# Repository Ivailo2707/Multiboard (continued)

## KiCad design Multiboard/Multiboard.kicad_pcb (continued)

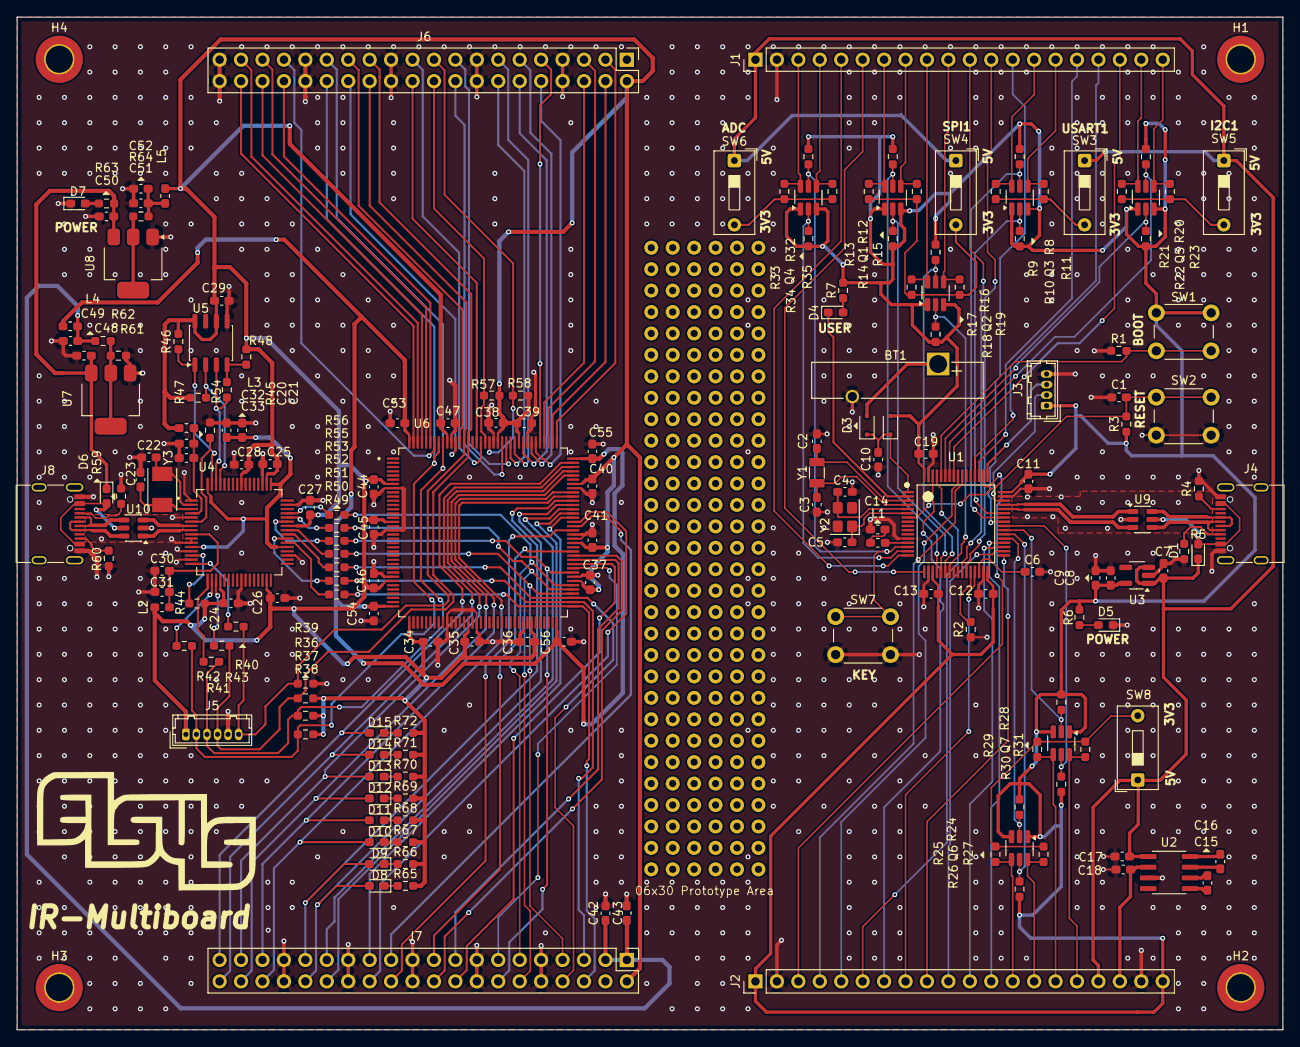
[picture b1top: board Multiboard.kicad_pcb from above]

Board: 2 copper layers, 150.0 x 120.0 mm, 190 parts (0 on the bottom side), 178 nets.

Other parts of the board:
06x30 Prototype Area: 6x30

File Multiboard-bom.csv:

"Reference","Qty","Value","DNP","Exclude from BOM","Exclude from Board","Footprint","LCSC Part Number"
"C1,C11,C12,C13,C14,C19","6","0.1u","","","","Capacitor_SMD:C_0603_1608Metric_Pad1.08x0.95mm_HandSolder","C14663"
"C2,C3","2","4.3pF","","","","Capacitor_SMD:C_0603_1608Metric_Pad1.08x0.95mm_HandSolder","C519375"
"C4,C5","2","12pF","","","","Capacitor_SMD:C_0603_1608Metric_Pad1.08x0.95mm_HandSolder","C38523"
"C6","1","2.2uF","","","","Capacitor_SMD:C_0603_1608Metric_Pad1.08x0.95mm_HandSolder","C913904"
"C7,C8,C17,C31,C33","5","4.7uF","","","","Capacitor_SMD:C_0603_1608Metric_Pad1.08x0.95mm_HandSolder","C19666"
"C9,C56","2","0.01uF","","","","Capacitor_SMD:C_0603_1608Metric_Pad1.08x0.95mm_HandSolder","C100042"
"C10,C20,C24,C25,C26,C27,C28,C29,C30,C32,C34,C35,C36,C37,C38,C39,C40,C41,C42,C43,C44,C45,C46,C47,C52,C53","26","0.1uF","","","","Capacitor_SMD:C_0603_1608Metric_Pad1.08x0.95mm_HandSolder","C14663"
"C15,C16","2","0.22uF","","","","Capacitor_SMD:C_0603_1608Metric_Pad1.08x0.95mm_HandSolder","C64705"
"C18","1","4.7uF","","","","Capacitor_SMD:C_0603_1608Metric_Pad1.08x0.95mm_HandSolder","C161217"
"C21,C48,C50,C55","4","10uF","","","","Capacitor_SMD:C_0603_1608Metric_Pad1.08x0.95mm_HandSolder","C19702"
"C22,C23","2","18pF","","","","Capacitor_SMD:C_0603_1608Metric_Pad1.08x0.95mm_HandSolder","C49326300"
"C49,C51","2","22uF","","","","Capacitor_SMD:C_0603_1608Metric_Pad1.08x0.95mm_HandSolder","C86295"
"C54","1","1uF","","","","Capacitor_SMD:C_0603_1608Metric_Pad1.08x0.95mm_HandSolder","C95843"
"D2,D3","2","D_Schottky","","","","Diode_SMD:D_SOD-323F","C2903903"
"D4,D7,D8,D9,D10,D11,D12,D13,D14,D15","10","GREEN","","","","LED_SMD:LED_0603_1608Metric_Pad1.05x0.95mm_HandSolder","C2994781"
"D5","1","RED","","","","LED_SMD:LED_0603_1608Metric_Pad1.05x0.95mm_HandSolder","C2846640"
"J4,J8","2","USB_C_Receptacle_USB2.0_16P","","","","Connector_USB:USB_C_Receptacle_G-Switch_GT-USB-7010ASV","C2988369"
"L1","1","10uH ±10%","","","","Inductor_SMD:L_0603_1608Metric_Pad1.05x0.95mm_HandSolder","C6808014"
"L2,L3,L4,L5","4","600ohm 500mA","","","","Inductor_SMD:L_0603_1608Metric_Pad1.05x0.95mm_HandSolder","C20345"
"Q1,Q2,Q3,Q4,Q5,Q6,Q7","7","Q_Dual_NMOS_G1S2G2D2S1D1","","","","Package_TO_SOT_SMD:SOT-23-6_Handsoldering","C404322"
"R1,R8,R9,R10,R11,R12,R13,R14,R15,R16,R17,R18,R19,R20,R21,R22,R23,R24,R25,R26,R27,R28,R29,R30,R31,R32,R33,R34,R35","29","10k","","","","Resistor_SMD:R_0603_1608Metric_Pad0.98x0.95mm_HandSolder","C98220"
"R2,R3,R46,R47,R48","5","10K","","","","Resistor_SMD:R_0603_1608Metric_Pad0.98x0.95mm_HandSolder","C98220"
"R4,R5,R6,R36,R37,R38,R59,R60","8","5.1K","","","","Resistor_SMD:R_0603_1608Metric_Pad0.98x0.95mm_HandSolder","C2907044"
"R7,R63,R65,R66,R67,R68,R69,R70,R71,R72","10","1K","","","","Resistor_SMD:R_0603_1608Metric_Pad0.98x0.95mm_HandSolder","C22548"
"R39,R44,R54,R57,R58","5","2.2K","","","","Resistor_SMD:R_0603_1608Metric_Pad0.98x0.95mm_HandSolder","C114662"
"R40,R41,R42,R43,R49,R50,R51,R52,R53,R55,R56,R62,R64","13","0","","","","Resistor_SMD:R_0603_1608Metric_Pad0.98x0.95mm_HandSolder","C95177"
"R45","1","12K 1%","","","","Resistor_SMD:R_0603_1608Metric_Pad0.98x0.95mm_HandSolder","C431727"
"R61","1","100","","","","Resistor_SMD:R_0603_1608Metric_Pad0.98x0.95mm_HandSolder","C105588"
"SW1","1","BOOT0","","","","Button_Switch_THT:SW_PUSH_6mm","C7528752"
"SW2","1","NRST","","","","Button_Switch_THT:SW_PUSH_6mm","C7528752"
"SW3,SW4,SW5,SW6,SW8","5","SW_SPST","","","","Button_Switch_THT:SW_DIP_SPSTx01_Slide_9.78x4.72mm_W7.62mm_P2.54mm","C41381904"
"SW7","1","KEY","","","","Button_Switch_THT:SW_PUSH_6mm","C7528752"
"U1","1","STM32F411RET6","","","","STM32F411RET6:QFP50P1200X1200X160-64N","C94355"
"U2","1","MAX662AESA_T","","","","MAX662AESA+T:SOIC127P600X175-8N","C2976348"
"U3","1","ME6211C33M5","","","","Package_TO_SOT_SMD:SOT-23-5_HandSoldering","C2984946"
"U4","1","FT2232HL-REEL","","","","FT2232HL:QFP50P1200X1200X160-64N","C27882"
"U5","1","93LCxxC","","","","Package_SO:SO-8_3.9x4.9mm_P1.27mm","C1350395"
"U7","1","AMS1117-1.2","","","","Package_TO_SOT_SMD:SOT-223","C14529"
"U8","1","NCP1117","","","","Package_TO_SOT_SMD:SOT-223","C20546"
"U9,U10","2","USBLC6-2SC6","","","","Package_TO_SOT_SMD:SOT-23-6","C7519"
"Y1","1","32.768KHz","","","","Crystal:Crystal_SMD_3215-2Pin_3.2x1.5mm","C95361"
"Y2","1","25MHz","","","","Crystal:Crystal_SMD_3225-4Pin_3.2x2.5mm","C255920"
"BT1","1","Battery_Cell","","Excluded from BOM","","Battery:Battery_Panasonic_CR2032-VS1N_Vertical_CircularHoles",""
"D1,D6","2","D","","Excluded from BOM","","Diode_SMD:D_0603_1608Metric_Pad1.05x0.95mm_HandSolder",""
"H1,H2,H3,H4","4","MountingHole_Pad_MP","","Excluded from BOM","","MountingHole:MountingHole_3.2mm_M3_DIN965_Pad_TopBottom",""
"J1,J2","2","Conn_01x20_Socket","","Excluded from BOM","","Connector_PinHeader_2.54mm:PinHeader_1x20_P2.54mm_Vertical",""
"J3","1","Debug","","Excluded from BOM","","Connector_Hirose:Hirose_DF13-04P-1.25DSA_1x04_P1.25mm_Vertical",""
"J5","1","Conn_01x06_Socket","","Excluded from BOM","","Connector_Hirose:Hirose_DF13-06P-1.25DSA_1x06_P1.25mm_Vertical",""
"J6,J7","2","Conn_02x20_Odd_Even","","Excluded from BOM","","Connector_PinHeader_2.54mm:PinHeader_2x20_P2.54mm_Vertical",""
"U6","1","LCMXO2-1200ZE-1TG144C","","Excluded from BOM","","LCMXO2-1200ZE-1TG144C:QFP50P2200X2200X160-144N",""
"Y3","1","12MHz","","Excluded from BOM","","Crystal:Crystal_SMD_TXC_7A-2Pin_5x3.2mm",""

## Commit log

2026-01-04 Added and wired first header roll and implemented BOOT0 block
2026-01-05 Wired second header row and added 1 ch bid level shifter symbol
2026-01-16 Added reset, power, rtc, level shifter and oscilator circuits
2026-01-18 Fixed sch bus and added 12V charge pump
2026-01-19 Put level shifters in nested schematic
2026-01-19 altered level shifter implementation
2026-01-21 Started PCB work
    Positioned mounting holes, pins and MCU, wired boot, reset buttons and ADC shifters
2026-01-21 FIxed level shifter implementation
2026-01-21 Fixed bus implementation
2026-01-22 changed mosfet footprint
2026-01-22 positioned and wired adc level shifter and decoupling capacitors
2026-01-23 positioned USART1 and I2C1 level shifters
2026-01-25 wired all level shifters and increased width of decoupling traces
2026-01-27 wired level shifters; positioed ldo and charge pump
2026-01-31 positioned and wired ldo charge pump buttons leds and rtc circuit
2026-02-01 wired most of the gpio pins
2026-02-05 Wired usb
2026-02-09 Implemented FTDI in schematic
2026-02-09 added and wired banks to the fpga schematic
2026-02-10 completed v1 FPGA schematic
2026-02-12 Added footprints and fixed schematic
2026-02-12 glitched schematic
2026-02-12 Completed mcu usb-c, mcu oscillators and mcu jtag pins
2026-02-14 positioned fpga-usb
2026-02-14 wired fpga usb
2026-02-14 positioned and wired FTDI
2026-02-15 placed decoupling capacitors around fpga
2026-02-15 synchronised sch and pcb. Added jtag connection between fpga and ftdi
2026-02-15 positioned ldo's and wired a few pins
2026-02-16 finished wiring all components
2026-02-16 test reverse polarity diode
2026-02-16 test reverse polarity
2026-02-16 wired power traces and added prototype area
2026-02-16 added copper zone on bot layer
2026-02-19 fixed fpga header issue
2026-02-19 fixed switch and led issue
2026-02-22 added silkscreen layer
2026-02-22 added elsys logo and project name to silkscreen
2026-02-23 fixed trace spacing issues in fpga pins
2026-03-13 cleared part of errors and warnings
2026-03-14 cleared thermal relief and solder mask errors
2026-03-16 added missing paths
2026-03-18 fixed dead copper zones and cleared all errors
2026-03-19 removed unused vias
2026-03-20 added top layer copper zone with stitiching vias, fixed trace issues and changed mcu pins footprint
2026-03-24 fixed missing fpga pins and added dedicated usb protection ic instead of diodes
2026-03-30 Fine tuning
2026-03-30 Fixed trace angle
2026-04-03 Generated BOM
2026-04-04 Added gbr drill bom and placement files
2026-04-04 added pick and place file
2026-04-06 fixed MCU LDO
2026-04-06 KiCAD glitch test
2026-04-07 Restored older version due to KiCAD glitching
2026-04-07 Fixed glitched nets issue
2026-04-07 Added final gbr bom and P&P
